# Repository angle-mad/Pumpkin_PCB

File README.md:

# Pumpkin_PCB
I made a PCB in the shape of a Pumpkin. 

# Schematic
Screenshot of the schematic in KiCad

# KiCad Screenshots
Screenshots of the front and back of the PCB in the KiCad 3D Viewer

# Falstad Simulation
I made a test circuit of the PCB on Falstad but with a potentiometer to simulate a photoresistor.

[Falstad Link](https://www.falstad.com/s.php?s=vxBJxa)

# Onshape
I used Onshape do to create to edge cuts for the pumpkin PCB. After sketching the area in Onshape I can export the sketch as DXF and import it into KiCad. I did this to make the edge cuts as well as some of the silkscreens and outline for the FR4 art.

# Krita
I used Krita to make silkscreen art of my Initials

# Features
- When the photoresistor is subject to the dark the 2 LEDs in the eyes will turn on and when not the LEDs should stay turned off
- When push button is held down the LED in the mouth will turn on until not held down
- PCB has custom made silkscreen art on front and back
- Pumpkin stem on PCB has exposed FR4 to differentiate it from the pumpkin body and I made a hole through it in order to make it a keychain

# BOM
| Item | Amount |
|---|---|
| CR2032 3V battery cell | 1 |
| CR2032 battery holder | 1 |
| 470Ω resistor | 3 |
| 4.7kΩ resistor | 1 |
| 47kΩ resistor | 1 |
| Photoresistor | 1 |
| 6mm push button | 1 |
| 2N3904 transistor | 1 |
| 5mm LED - Red | 2 |
| 5mm LED - Yellow | 1 |

Made by @Angel M on slack

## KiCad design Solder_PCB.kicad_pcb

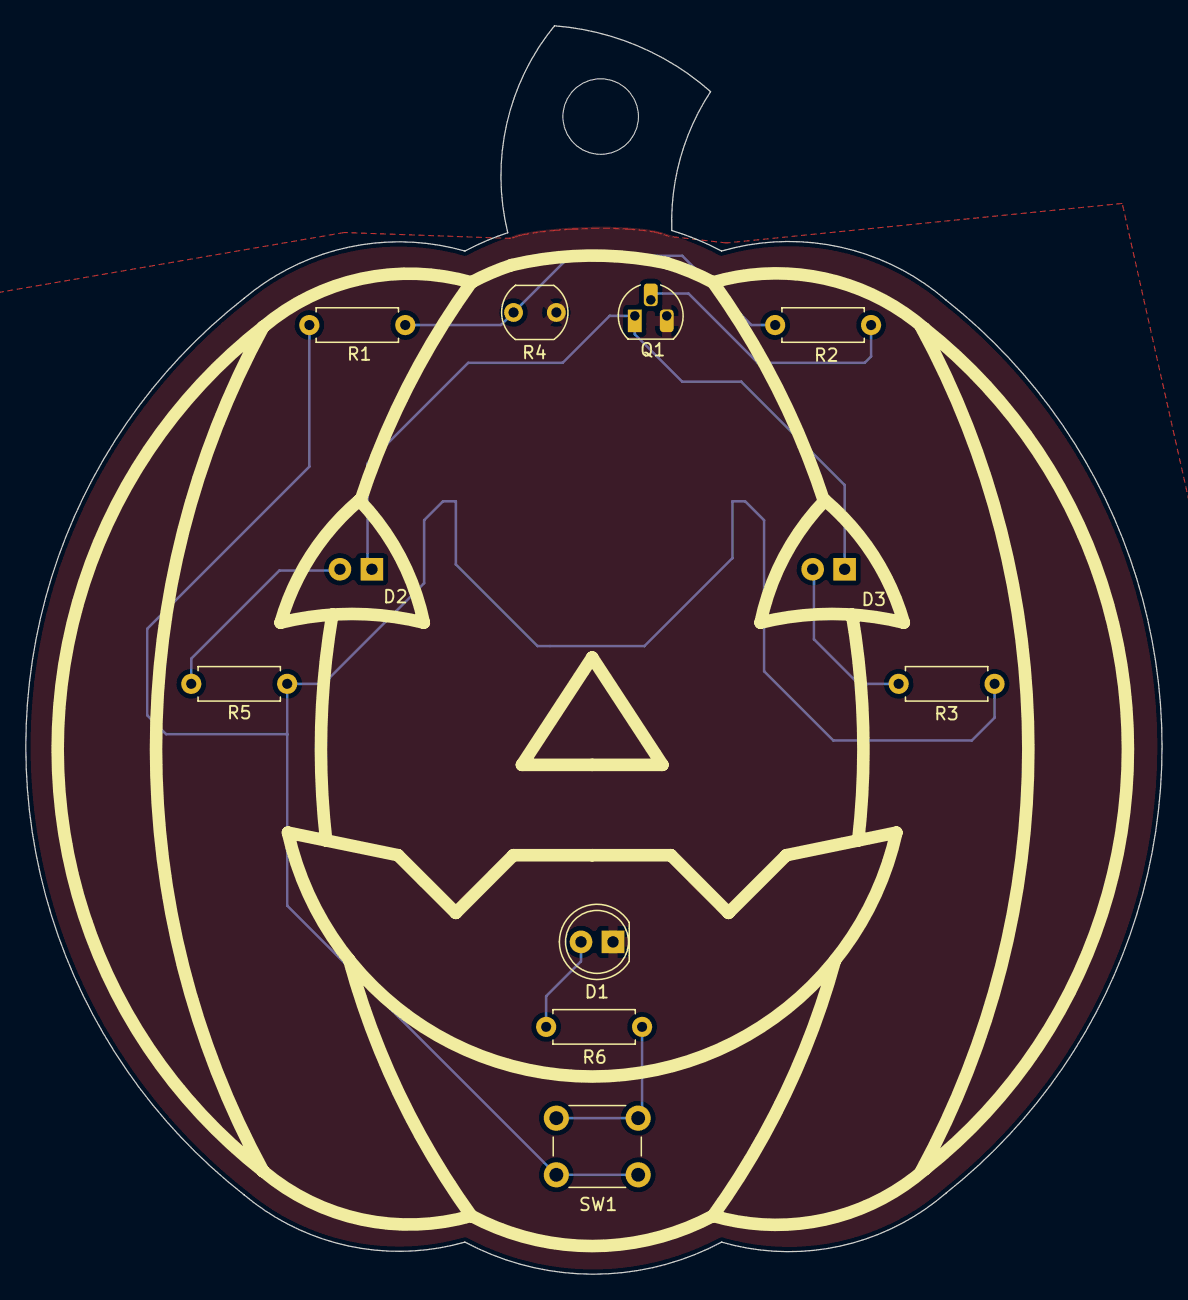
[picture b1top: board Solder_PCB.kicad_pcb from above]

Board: 2 copper layers, 90.3 x 99.2 mm, 12 parts (1 on the bottom side), 9 nets.

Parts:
BT1: Battery_Cell; BatteryHolder_Keystone_3034_1x20mm
D1, D2, D3: LED; LED_D5.0mm
Q1: NPN; TO-92L_HandSolder
R1, R2, R3, R5, R6: R; R_Axial_DIN0207_L6.3mm_D2.5mm_P7.62mm_Horizontal
R4: R_Photo; R_LDR_5.1x4.3mm_P3.4mm_Vertical
SW1: SW_Push; SW_PUSH_6mm

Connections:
GND: BT1.2 (-), D1.1 (K), Q1.3 (E), R4.2
unnamed: BT1.1 (+), R1.1, R3.1, R5.2, SW1.2
unnamed: D1.2 (A), R6.1
unnamed: D2.2 (A), R5.1
unnamed: D2.1 (K), D3.1 (K), Q1.1 (C)
unnamed: D3.2 (A), R3.2
unnamed: Q1.2 (B), R2.2
unnamed: R1.2, R2.1, R4.1
unnamed: R6.2, SW1.1

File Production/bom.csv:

Designator,Footprint,Quantity,Value,LCSC Part #
BT1,BatteryHolder_Keystone_3034_1x20mm,1,Battery_Cell,
"D1, D2, D3",LED_D5.0mm,3,LED,
Q1,TO-92L_HandSolder,1,NPN,
"R1, R2, R3, R5, R6",R_Axial_DIN0207_L6.3mm_D2.5mm_P7.62mm_Horizontal,5,R,
R4,R_LDR_5.1x4.3mm_P3.4mm_Vertical,1,R_Photo,
SW1,SW_PUSH_6mm,1,SW_Push,
